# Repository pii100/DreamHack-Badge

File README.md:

# DreamHack-Badge

Files for dreamhack badge PCBs

Currently based on ESP32-WROOM MCU with MSP3217 display and APA102 5050 leds

Both display and leds may change based on budget

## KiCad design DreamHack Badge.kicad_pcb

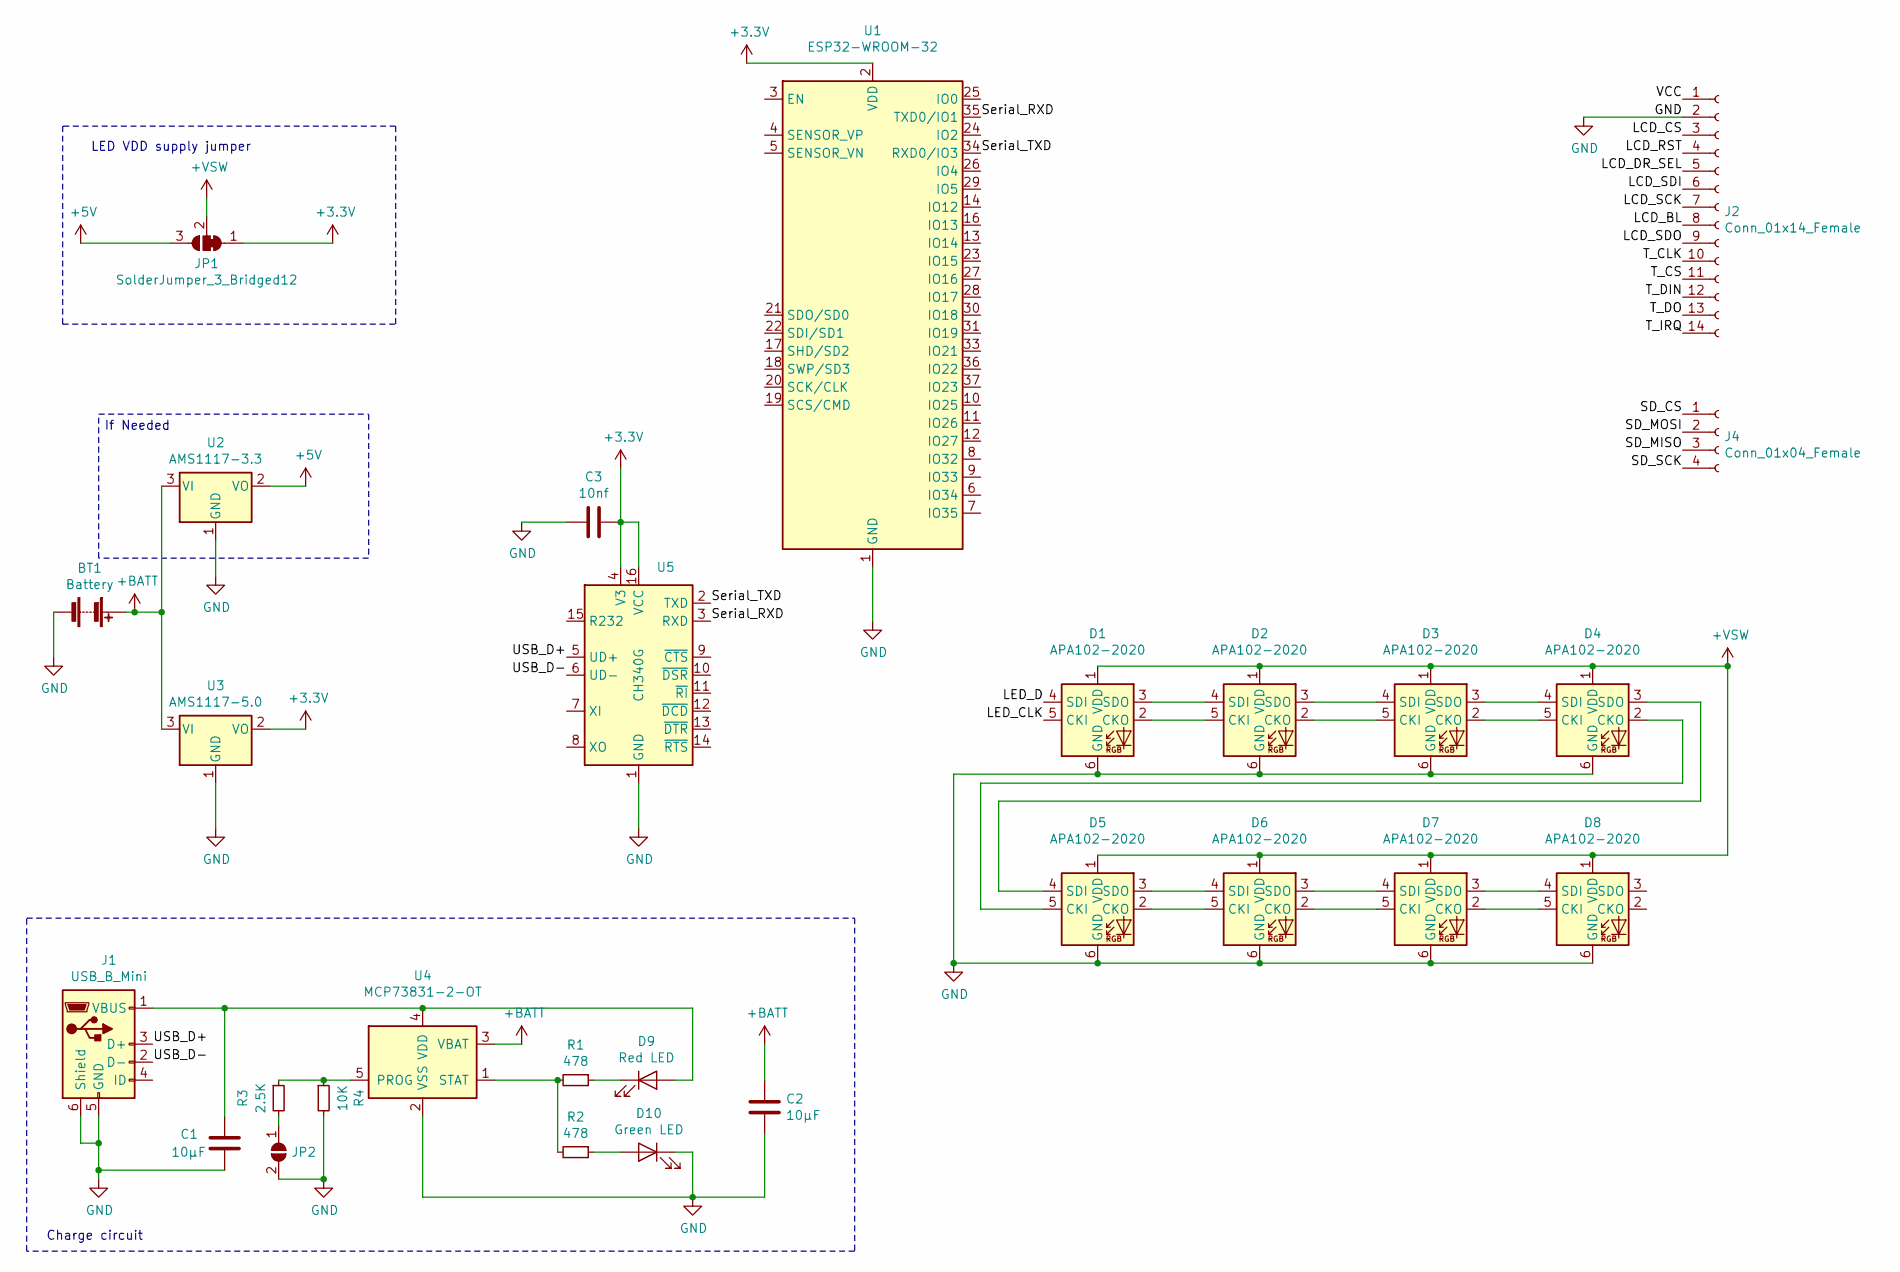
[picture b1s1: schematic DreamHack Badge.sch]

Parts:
BT1: Battery; JST_PH_S2B-PH-K_1x02_P2.00mm_Horizontal
C1, C2: 10μF; C_0805_HandSoldering
C3: 10nf; C_0805_HandSoldering
D1, D2, D3, D4, D5, D6, D7, D8: APA102-2020; LED-APA102-2020
D9: Red LED; LED_0805_HandSoldering
D10: Green LED; LED_0805_HandSoldering
J1: USB_B_Mini; USB_Mini-B
J2: Conn_01x14_Female; Pin_Header_Straight_1x14_Pitch2.54mm
J4: Conn_01x04_Female; Pin_Header_Straight_1x04_Pitch2.54mm
JP1: SolderJumper_3_Bridged12; SolderJumper-3_P1.3mm_Bridged12_RoundedPad1.0x1.5mm
JP2: SolderJumper_2_Open; SolderJumper-2_P1.3mm_Open_RoundedPad1.0x1.5mm
R1, R2: 478; R_0805_HandSoldering
R3: 2.5K; R_0805_HandSoldering
R4: 10K; R_0805_HandSoldering
U1: ESP32-WROOM-32
U2: AMS1117-3.3; SOT-223-3_TabPin2
U3: AMS1117-5.0; SOT-223-3_TabPin2
U4: MCP73831-2-OT; TSOT-23-5_HandSoldering
U5: CH340G; SOIC-16_3.9x9.9mm_P1.27mm

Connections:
+3V3: C3.1, JP1.1 (A), U1.2 (VDD), U3.2 (VO), U5.4 (V3), U5.16 (VCC)
+5V: JP1.3 (B), U2.2 (VO)
+BATT: BT1.1 (+), C2.1, U2.3 (VI), U3.3 (VI), U4.3 (VBAT)
+VSW: D1.1 (VDD), D2.1 (VDD), D3.1 (VDD), D4.1 (VDD), D5.1 (VDD), D6.1 (VDD), D7.1 (VDD), D8.1 (VDD), JP1.2 (C)
/LCD_BL: J2.8
/LCD_CS: J2.3
/LCD_DR_SEL: J2.5
/LCD_RST: J2.4
/LCD_SCK: J2.7
/LCD_SDI: J2.6
/LCD_SDO: J2.9
/LED_CLK: D1.5 (CKI)
/LED_D: D1.4 (SDI)
/SD_CS: J4.1
/SD_MISO: J4.3
/SD_MOSI: J4.2
/SD_SCK: J4.4
/Serial_RXD: U1.35 (TXD0/IO1), U5.3 (RXD)
/Serial_TXD: U1.34 (RXD0/IO3), U5.2 (TXD)
/T_CLK: J2.10
/T_CS: J2.11
/T_DIN: J2.12
/T_DO: J2.13
/T_IRQ: J2.14
/USB_D+: J1.3 (D+), U5.5 (UD+)
/USB_D-: J1.2 (D-), U5.6 (UD-)
/VCC: J2.1
GND: BT1.2 (-), C1.2, C2.2, C3.2, D1.6 (GND), D2.6 (GND), D3.6 (GND), D4.6 (GND), D5.6 (GND), D6.6 (GND), D7.6 (GND), D8.6 (GND), D10.1 (K), J1.5 (GND), J1.6 (Shield), J2.2, JP2.2 (B), R4.2, U1.1 (GND), U1.15 (GND), U1.38 (GND), U2.1 (GND), U3.1 (GND), U4.2 (VSS), U5.1 (GND)
unnamed: C1.1, D9.2 (A), J1.1 (VBUS), U4.4 (VDD)
unnamed: D1.2 (CKO), D2.5 (CKI)
unnamed: D1.3 (SDO), D2.4 (SDI)
unnamed: D2.2 (CKO), D3.5 (CKI)
unnamed: D2.3 (SDO), D3.4 (SDI)
unnamed: D3.2 (CKO), D4.5 (CKI)
unnamed: D3.3 (SDO), D4.4 (SDI)
unnamed: D4.2 (CKO), D5.5 (CKI)
unnamed: D4.3 (SDO), D5.4 (SDI)
unnamed: D5.2 (CKO), D6.5 (CKI)
unnamed: D5.3 (SDO), D6.4 (SDI)
unnamed: D6.2 (CKO), D7.5 (CKI)
unnamed: D6.3 (SDO), D7.4 (SDI)
unnamed: D7.2 (CKO), D8.5 (CKI)
unnamed: D7.3 (SDO), D8.4 (SDI)
unnamed: D9.1 (K), R1.1
unnamed: D10.2 (A), R2.1
unnamed: JP2.1 (A), R3.2
unnamed: R1.2, R2.2, U4.1 (STAT)
unnamed: R3.1, R4.1, U4.5 (PROG)

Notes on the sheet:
LED VDD supply jumper
Charge circuit
If Needed

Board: 2 copper layers, 28 parts (15 on the bottom side), 29 nets, no tracks yet.

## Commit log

2019-06-05 fixed footprints
2019-06-05 fixed apa102 refs
2019-06-05 basic pcb layout
2019-06-05 updated readme with part numbers
2019-06-05 updated pcb, added cutout and moved esp to back
2019-06-05 updated schematic, added power side
2019-06-06 updated gitignore and remvoed cache and bak files
2019-06-06 added ch340 usb to serial for direct flshing
2019-06-06 Updated PCB with power and serial components
